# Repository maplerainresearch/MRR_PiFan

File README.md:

# MRR PiFan
Slim fan controller module for single board computers

For controlling the fan, you can use a script, like this one ([Pi Fan Controller](https://github.com/Howchoo/pi-fan-controller)).

The module can be used as a mini-hat too.

See this [blog post](https://teck78.blogspot.com/2020/04/mrr-pifan-slim-fan-controller-for.html) for more information.

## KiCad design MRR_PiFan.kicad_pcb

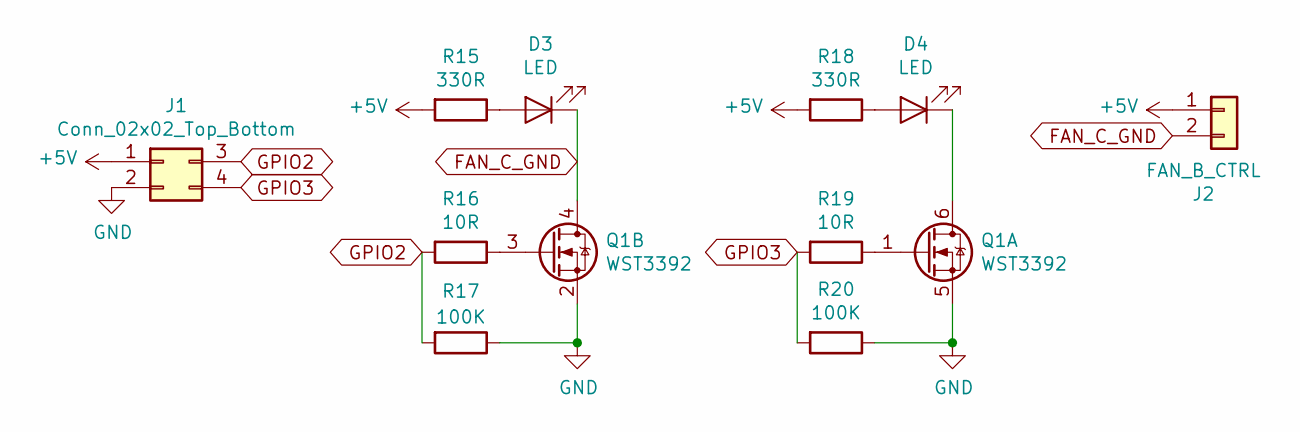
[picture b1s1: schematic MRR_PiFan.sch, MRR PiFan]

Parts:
D3, D4: LED; LED_0805_2012Metric_Pad1.15x1.40mm_HandSolder; Mfg part no. 17-21SURC/S530-A3/TR8; LCSC Part Number C72037
J1: Conn_02x02_Top_Bottom; PinSocket_2x02_P2.54mm_Vertical; Mfg part no. C47553; LCSC Part Number C47553
J2: FAN_B_CTRL; PinHeader_1x02_P2.54mm_Vertical; Mfg part no. MTB125-1102R1; LCSC Part Number C3761205
Q1: WST3392; SOT-23-6_Handsoldering; Mfg part no. WST3392; LCSC Part Number C148366
R15, R18: 330R; R_0805_2012Metric; Mfg part no. 0805W8F3300T5E; LCSC Part Number C17630
R16, R19: 10R; R_0805_2012Metric; Mfg part no. 0805W8F100JT5E; LCSC Part Number C17415
R17, R20: 100K; R_0805_2012Metric; Mfg part no. 0805W8F1003T5E; LCSC Part Number C149504

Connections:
+5V: J1.1, J2.1, R15.2, R18.2
FAN_C_GND: D3.1 (K), J2.2, Q1.4 (D)
GND: J1.2, Q1.2 (S), Q1.5 (S), R17.1, R20.1
GPIO2: J1.3, R16.2, R17.2
GPIO3: J1.4, R19.2, R20.2
unnamed: D3.2 (A), R15.1
unnamed: D4.1 (K), Q1.6 (D)
unnamed: D4.2 (A), R18.1
unnamed: Q1.1 (G), R19.1
unnamed: Q1.3 (G), R16.1

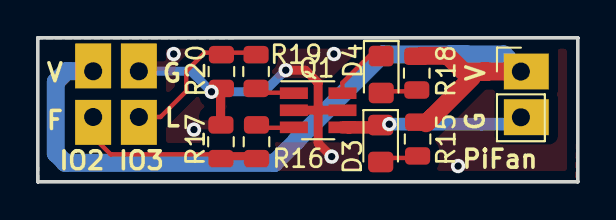
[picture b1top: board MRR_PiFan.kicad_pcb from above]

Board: 2 copper layers, 30.0 x 8.0 mm, 11 parts (1 on the bottom side), 10 nets.

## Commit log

2020-04-10 Added initial version
2020-09-26 Added fan control scripts

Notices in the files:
MRR_PiFan.kicad_pcb:
under CERN OHL v.1.2
